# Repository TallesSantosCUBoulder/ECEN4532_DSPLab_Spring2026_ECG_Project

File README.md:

# Module 02 – ECG Project
**ECEN4532: Digital Signal Processing Laboratory (Spring 2026)**  
**Instructor:** Talles Santos  
**Students:**   Alyssa Jackson  
&emsp;&emsp;&emsp;&emsp;&emsp;Joshua Thomas  
&emsp;&emsp;&emsp;&emsp;&emsp;Emilie Teel  

## Introduction
  An electrocardiogram (often shortened to ECG or EKG) procedure is a quick and simple test that is designed to record the eletrical signal from a patient's beating heart and use it to find its natural rhythmic cycle [1]. By placing electrodes aroud the patient's chest, arms, and/or legs, a circuit is created with the heart as the voltage source the contractions caused by electricity are pickeed up by the electrodes and sent to a circuit.

  *Figure 1: A diagram of the different parts of a heartbeat that are searched for during an ECG test [2].*  

  This signal of the heartbeat, in the form of the "PQRST" complex as seen with Figure 1, is what needs to be detected in order to find important information about a patient's heart. Things like poor blood flow, arrhythmias, heart attacks, and thickened heart walls, can be picked up, seen, and diagnosed accurately with this type of circuit [4].  

  The goal of this project is not only to build an analog circuit that can pick up the signals of a heartbeat, but to then transmit that data using an Arduino Uno to MATLAB that will then visual said data from the heart and calculate the BPM (or the beats per minute) from the received signal.

## Methodology

### Hardware

*Figure 2: A diagram of the circuit that a body completes based on the position of the electrodes. A) represents the circuit on a body while B) shows the connections in the image space. [3]*  

As can be seen in Figure 2, the basic premise of the ECG Circuit itself involves building a voltage divider with the heart in order to pick up the signals ans input it into the circuit.

#### Circuit Schematic

To gather the heart rate information from the body leads are attatched to the patient and then connected to an analog circuit to filter and amplify the data coming in from the leads. This circuit is used as a form of preprocessing to alow for a more precise reading from the microcontroller. Below is the schematic of the ECG circuit that was used in its design.

The Schematic of the circuit is broken into parts each playing a role in the amplification, filtering, or offset of the signal for later interpretation. The first segment of the schematic is an instrumentation amplifier to take the very weak signal from the body and give it gain to allow for filtering. The second step is a passive high pass filter made of a capacitor and resistor. This stage is used to reduce interferance from body roll and breathing, and to remove dc offset from the signal. The next stage is a buffer to isolate previos stages from feedback. The following stage is a 60hz notch filter. This filter has a high attenuation of the 60 hz signal to remove interferance from main powr in the room as it is the biggest source of interferance in the signal. This is then fed into a buffer to once again isolate the filter from future stages. The subsiquent stage is an active low pass filter to further attenuate high frequencies such as 60hz and to remove any noise from frequencies not produced by heartrate. The final stage is an inverting amplifier to further amplify the signal for processing, and it is combined with a circuit to add offset so the microcontroller can read the signal.

#### PCB Design

To buid the circuit in hardware the schematic was then used to design the PCB to physically implement the circuit. Below is the PCB schematic that was used in this project.

There was an itterative process used in designing the layout for the PCB. The software used for this was KICAD, and in this software it has the ability to select pieces from the schematic to then place on the PCB. So the circuit was designed piece by piece for each module. The circuit looped arround starting at the bottom left corner with the inputs and moving on to the top left for the output. each of the op amps used were dual op amps and therefor the sequential modules were able to make use of the two amplifiers vutting down on the size of the circuit. The difficult part of the design was making sure that all power inputs and ground planes were connected propperly. Through trial and error the above circuit was compiled.

The hardware was not able to be completed at the time of this paper, but the components have been selected and they will be soldered to the pcb to complete the analog circuit.
### Testing the Hardware

At the time of this paper the circuit was not able to be made due to some issues with the milling machine, but there are further steps for future use when the machine is up and running. The future plans for testing is to print out the PCB, solder on the components, and connect the completed circuit to the simulator and then to one of us to test the output. The output of the circuit will be observed from the ocilloscope and a passed test will be a test that shows a similar result to the already working breadboard circuit. The report will be updated with this information when the tests have been run.
### Software
For the software side of things, an Arduino Uno R3 was used to take that normalized heartbeat signal, or a simple test signal generated from a function generator, that ranges from 0 to 5V and transmit the data to MATLAB via packets. The packets act like individual bundles of data that are all sent to the host computer running MATLAB in order instead of in a constant real time stream that would take more processing power and lead to potential data errors.  

But before the data is sent over, the MATLAB script must be formatted to in order to gather the data coming in from the Arduino at the correct speed and sampling frequency:  

```matlab
% define port; check whatever port the Arduino is connected to
% and uncomment that one while commenting the other ports
portName = serialportlist("available");
% portName = '/dev/ttyACM0' ;
% portName = '/dev/ttyACM1' ;
portName = '/dev/ttyUSB0' ;

% open port
fp = serialport(portName,115200);

% settings
fs = 1 / (3e-3) ;                          % sampling frequency of the arduino
sizeBufferArduino = 20 ;                   % from arduino code
t_Buffer = 10.0 ;                          % in seconds
nSamplesBuffer = round(t_Buffer*fs) ;      % nSamples of the circular buffer in the matlab script
bits2volts = 5/(2^10-1) ;                  % convertion from bits to volts (arduino uno 10 bits)

% initialing variables
CircularBuffer = zeros(nSamplesBuffer,1);
vecSamples = 0 ;
count=1;

``` 
*Code Snipet 1: The first lines from the MATLAB script 'read_serial_Nsamples_buffer.m'. These lines work to format everything from the baud rate being received, the sampling frequency that the signal is being measured at, the size of the data packets that are recieved at once, conversion of the Arduino value from 0 to 5 volts, and other variables needed in the plotting of the data in real-time.* 

That packet of 20 individual values from the Arduino is sent to a loop that can't be left without a Serial port disconnection or a manual code end caused by the user. That loop constantly looks for the start of the new incoming packet, packet into a vector that MATLAB can tranversed, enters that vector being evaluated, turns the value into a voltage thanks to the data conversion with a time attached to the value, and finally plotted on a constantly updating graph of voltage vs. time. A circular buffer is used so that a constant stream of voltages can be plotted in an ever-rotating plot that can be seen in Figure 3 below.

*Figure 3: A gif that shows how the plotting of data works on MATLAB. The red vertical line acts as the real-time sweep as the signal gets plotted.*  

As can also be seen from Figure 3, there are also magneta dots and red and green stars on the signal as well. These are the marks that are meant to point to the what the R peak of a signal is as well as the right(green) and left(red) of that R peak, as explained below:

```matlab
% For the best and most accurate data, the inputted signal need to be 
% filtered first
function [R_loc, left, right, bpm]=identifyQRSComplex(signal,Fs)

R_loc = [];
left = [];
right = [];
bpm = NaN;
%% Preprocessing the signal for QRS detection
x = signal;

% Removing the DC Offset from the Signal
x = x - mean(x);

% Finding the Time Scale of the Signal
T = 1/Fs;
N = length(x);

t = (0:N-1)*T;

% Normalizing the Signal
Norm_signal = x.^2;
Norm_signal = Norm_signal / max(abs(Norm_signal));

% Finding the QRS Complex Peaks
h = ones (1,36)/36; % 0.1secs
% Apply filter
x = conv (Norm_signal ,h,'same');
x = x/max(abs(x));

max_h = max(x);
thresh = 2*mean(x);
poss_reg =(x>thresh*max_h)';

% left = find(diff([0 poss_reg'])==1);
% right = find(diff([poss_reg' 0])==-1);

if isempty(poss_reg)
      left = [];
      right = [];
    else
      left = find(diff([0, poss_reg(:)']) == 1);
      right = find(diff([poss_reg(:)' 0]) == -1);
end

% The R_loc variable is the location of the R values that make up a QRS
% Complex
for i=1:length(left)
    [R_value(i) R_loc(i)] = max(x(left(i):right(i)));
    R_loc(i) = R_loc(i)-1+left(i); % add offset
end

freq_heartbeat = length(left)/max(t);

% Convert frequency to beats per minute
bpm = freq_heartbeat * 60;

end
```
*Code Snipet 2: The 'identifyQRSComplex' function used in the MATLAB code to find the bpm, the R location from the QRS complex, and the left and right of the the R location.*  

The code from the above snipet is the entireity of the function, and it also has the added benefit of being able to calculate the bpm (or the frequency of a signal in the span of a minute) of the input signal, which is displayed at the top of the gif in Figure 3. When combined, the function from Code Snipet 2 and the MATLAB script, the entirity of the code can detect the peaks of a signal, mark its highest point, the immediate left and right of that peak, and the BPM (or the frequency per minute for non-heartbeat signals) of the signal that is detected through the Arduino Uno.

### Testing the Software

Testing the programming for both the Arduino and MATLAB itself is pretty simple: connect the Arduino to PC running the MATLAB script and view the real-time output from the A0 pin.  

*Figure 4: A gif that shows how the plotting of signals to MATLAB. The gif shows the signals from the A0 pin connected to the GND pin, the 5V pin, and just open to the air.*  

As shown with Figure 4, the signal from the Arduino in the different inputs to the A0 pin. In this test, the BPM from the signal means nothing since the Arduino updating from the inputs was slow due to the packets method, so a different test would be needed to see how the BPM calculation would work.  

*Figure 5: The settings used for the test signal input in the Arduino.*  

Instead of just having a DC signal and moving it from 5V to GND very fast by hand, a function generator was used instead and set with the parameter as seen in Figure 5. The gif from Figure 3 is the real-time plotting of the signal generated using the information from Figure 5.

*Figure 6: The image from the MATLAB srcipt running that shows the BPM of the signal, which is around 90 times a second for a minute, or around 1.5Hz.*  

While the BPM can be seen in Figure 3, it is shown again ib Figure 6. The BPM can be seen as 90, or 1.5Hz, which lines up with how the function generator was set up to output. This shows that the BPM calculation, and the software side of the ECG circuit as a whole, is working as intended.

### Connecting the Hardware and Software

## Results

*Figure 7: The image from the MATLAB srcipt running that shows the BPM of the generated heartbeat signal, which is around 60 times per minute, or around 1Hz.*  

Once the circuit board was connected to the Arduino or MATLAB, and the output from Figure 7 with the same BPM as generated from the heartbeat signal generator, it shows that the system works. Despite the little hiccup of the R location marker where the marker is on the lower S spike instead of the R peak, the count of the BPM and the output of the entire system is correct and show that everything works.  

## Conclusion and Future Work

With the overall results of the completed hardware and software integration showing that the accurate heartbeat shape normalized in between 0 and 5V and counting same BPM value that the heartbeat device, it is safe to say that the overall circuit works. Every apsect does what it is supposed to do, despite some flaws.  

The main issues that were had with the ECG circuit as a whole was the slow speed of the "real-time" system and the fact that the MATLAB script counts the bottom part of the QRS complex instead of the R peak like it should. The slow "real-time" data collection issue can be solved with a faster, more powerful computer. The R peak detection, on the other hand, is due to the fact that the heartbeat signal generator isn't completely accurate to an actual heartbeat. An actual heartbeat looks more like the image from Figure 1, with the S peak in the QRS complex being nowhere as large as what the heartbeat generator outputs in normal heartbeats. While most ECG images do look like Figure 1, there are some situations, either with abnormal heartbeats or with the placements of the electrodes [5, 6], a large S peak can occur and have a larger value than the R peak. Due to this oversight in assumption of the QRS complex that has then bleed into the Code Snipet 2 with the 'identityQRSComplex' function, a fix that needs to not only look into the value of the peak but into the positive value while having better checks with the Q and S peaks to better mark on the plot of the signal would be the next step to take. But other than that, this combination of hardware signal detection, filtering, and normalization to software real-time QRS complex detection and BPM calculation works overall.

Due to manufacturing error, the circuit was not completely implemented at the time of this report. Future steps in this reguard are to fix the milling machine by replacing the bits, milling out the PCB, soldering the components, and testing the circuit as related in the testing portion of this report. The hardware and software when both verified to be working will be combined to a full implementation, and the further software implementations will be added. 

## References
[1]&emsp;Mayo Clinic, “Electrocardiogram (ECG or EKG),” Mayoclinic.org, Apr. 02, 2024. https://www.mayoclinic.org/tests-procedures/ekg/about/pac-20384983
‌

[2]&emsp;“How does an ECG work? Understanding ECG and heart health,” Withings.com, 2026. https://www.withings.com/us/en/health-insights/about-ecg-ekg-electrocardiogram?srsltid=AfmBOorydm8yKYhquxItaWKUVDFjAmXBAV8dxPpUkZrdyCu7soVGj3wy (accessed Mar. 22, 2026).
‌

[3]&emsp;Jaakko Malmivuo and R. Plonsey, Bioelectromagnetism : Principles and Applications of Bioelectric and Biomagnetic Fields. New York Oxford University Press -10-05, 1995.
‌

[4]&emsp;“Abnormal Electrocardiogram (ECG/EKG) - Doral Health & Wellness NY,” Doral Health & Wellness, Aug. 08, 2025. https://doralhw.org/condition/abnormal-electrocardiogram-ecg-ekg/ (accessed Mar. 22, 2026).
‌

[5]&emsp;About EMCrit, “Late or irregular R-wave transition,” EMCrit Project, Aug. 07, 2025. https://emcrit.org/ibcc/later/ (accessed Mar. 23, 2026).
‌

[6]&emsp;“The QRS complex: ECG features of the Q-wave, R-wave, S-wave & duration,” ECG & ECHO, May 22, 2018. https://ecgwaves.com/ecg-qrs-complex-q-r-s-wave-duration-interval/
‌

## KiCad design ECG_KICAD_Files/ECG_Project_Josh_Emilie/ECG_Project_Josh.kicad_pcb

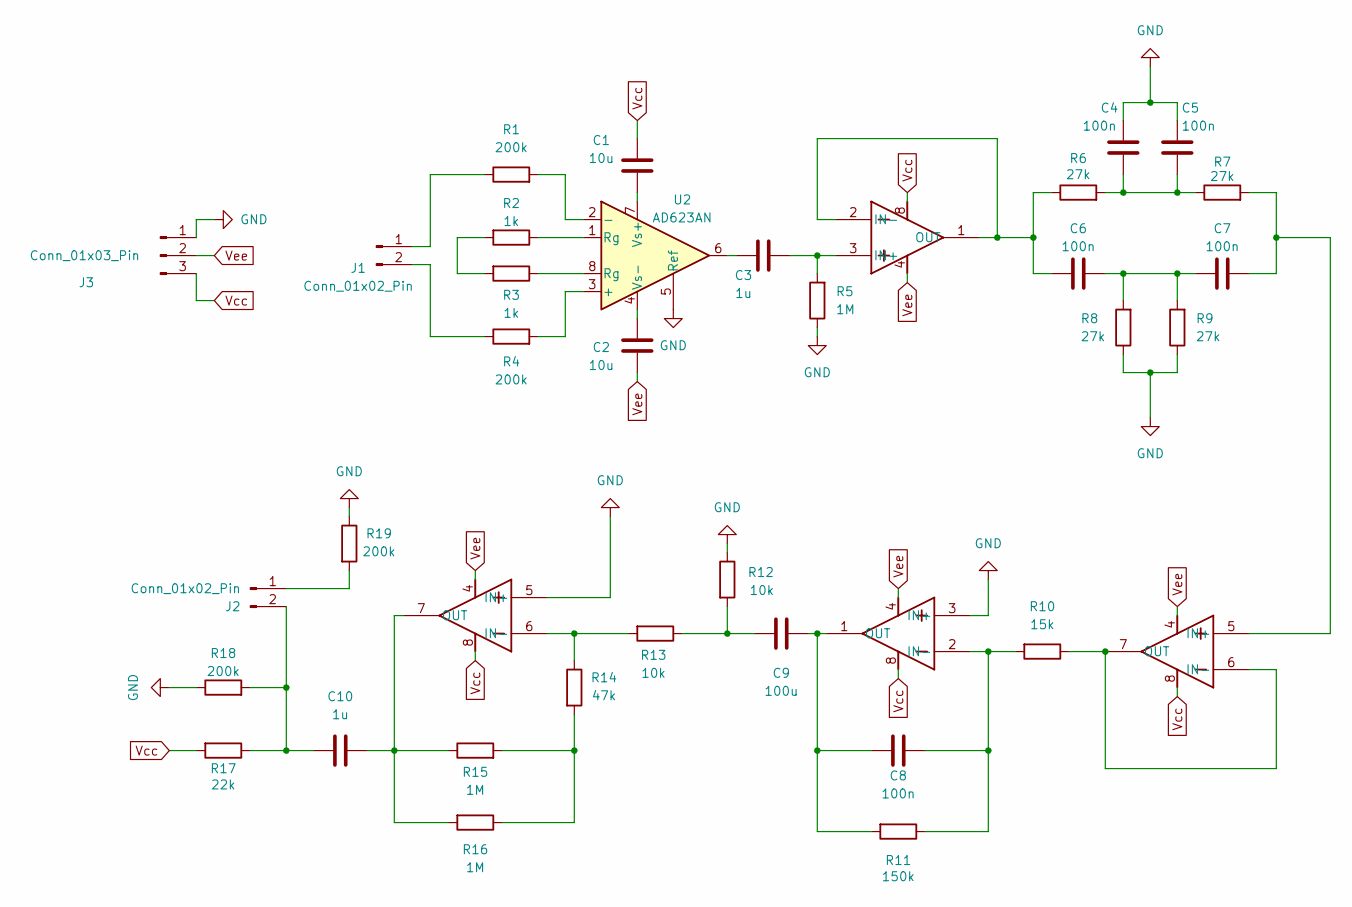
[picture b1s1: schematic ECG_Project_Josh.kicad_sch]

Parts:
C1, C2: 10u; C_Axial_L3.8mm_D2.6mm_P7.50mm_Horizontal
C3, C10: 1u; C_Axial_L3.8mm_D2.6mm_P7.50mm_Horizontal
C4, C5, C6, C7, C8: 100n; C_Axial_L3.8mm_D2.6mm_P7.50mm_Horizontal
C9: 100u; C_Axial_L3.8mm_D2.6mm_P7.50mm_Horizontal
J1, J2: Conn_01x02_Pin; PinHeader_1x02_P2.54mm_Horizontal
J3: Conn_01x03_Pin; PinHeader_1x03_P2.54mm_Horizontal
R1, R4, R18, R19: 200k; R_Axial_DIN0204_L3.6mm_D1.6mm_P7.62mm_Horizontal
R2, R3: 1k; R_Axial_DIN0204_L3.6mm_D1.6mm_P7.62mm_Horizontal
R5, R15, R16: 1M; R_Axial_DIN0204_L3.6mm_D1.6mm_P7.62mm_Horizontal
R6, R7, R8, R9: 27k; R_Axial_DIN0204_L3.6mm_D1.6mm_P7.62mm_Horizontal
R10: 15k; R_Axial_DIN0204_L3.6mm_D1.6mm_P7.62mm_Horizontal
R11: 150k; R_Axial_DIN0204_L3.6mm_D1.6mm_P7.62mm_Horizontal
R12, R13: 10k; R_Axial_DIN0204_L3.6mm_D1.6mm_P7.62mm_Horizontal
R14: 47k; R_Axial_DIN0204_L3.6mm_D1.6mm_P7.62mm_Horizontal
R17: 22k; R_Axial_DIN0204_L3.6mm_D1.6mm_P7.62mm_Horizontal
U1, U3: LF412ACN/NOPB; DIP-8_W7.62mm
U2: AD623AN; DIP-8_W7.62mm

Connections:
GND: C4.2, C5.2, J3.1, R5.1, R8.1, R9.1, R12.1, R18.1, R19.1, U2.5 (Ref), U3.3 (IN+), U3.5 (IN+)
unnamed: C3.1, U2.6
unnamed: C4.1, C5.1, R6.2, R7.1
unnamed: C6.1, C7.2, R8.2, R9.2
unnamed: C9.2, R12.2, R13.1
unnamed: J1.1, R1.1
unnamed: J1.2, R4.1
unnamed: J2.1, R19.2
unnamed: C10.1, J2.2, R17.1, R18.2
unnamed: R2.1, U2.1 (Rg)
unnamed: R2.2, R3.2
unnamed: R3.1, U2.8 (Rg)
unnamed: R14.2, R15.2, R16.1
unnamed: C3.2, R5.2, U1.3 (IN+)
unnamed: C6.2, R6.1, U1.1 (OUT), U1.2 (IN-)
unnamed: C7.1, R7.2, U1.5 (IN+)
unnamed: R10.1, U1.6 (IN-), U1.7 (OUT)
unnamed: R4.2, U2.3 (+)
unnamed: R1.2, U2.2 (-)
unnamed: C1.2, U2.7 (Vs+)
unnamed: C2.2, U2.4 (Vs-)
unnamed: C8.1, R10.2, R11.1, U3.2 (IN-)
unnamed: C8.2, C9.1, R11.2, U3.1 (OUT)
unnamed: R13.2, R14.1, U3.6 (IN-)
unnamed: C10.2, R15.1, R16.2, U3.7 (OUT)
Vcc: C1.1, J3.3, R17.2, U1.8, U3.8
Vee: C2.1, J3.2, U1.4, U3.4

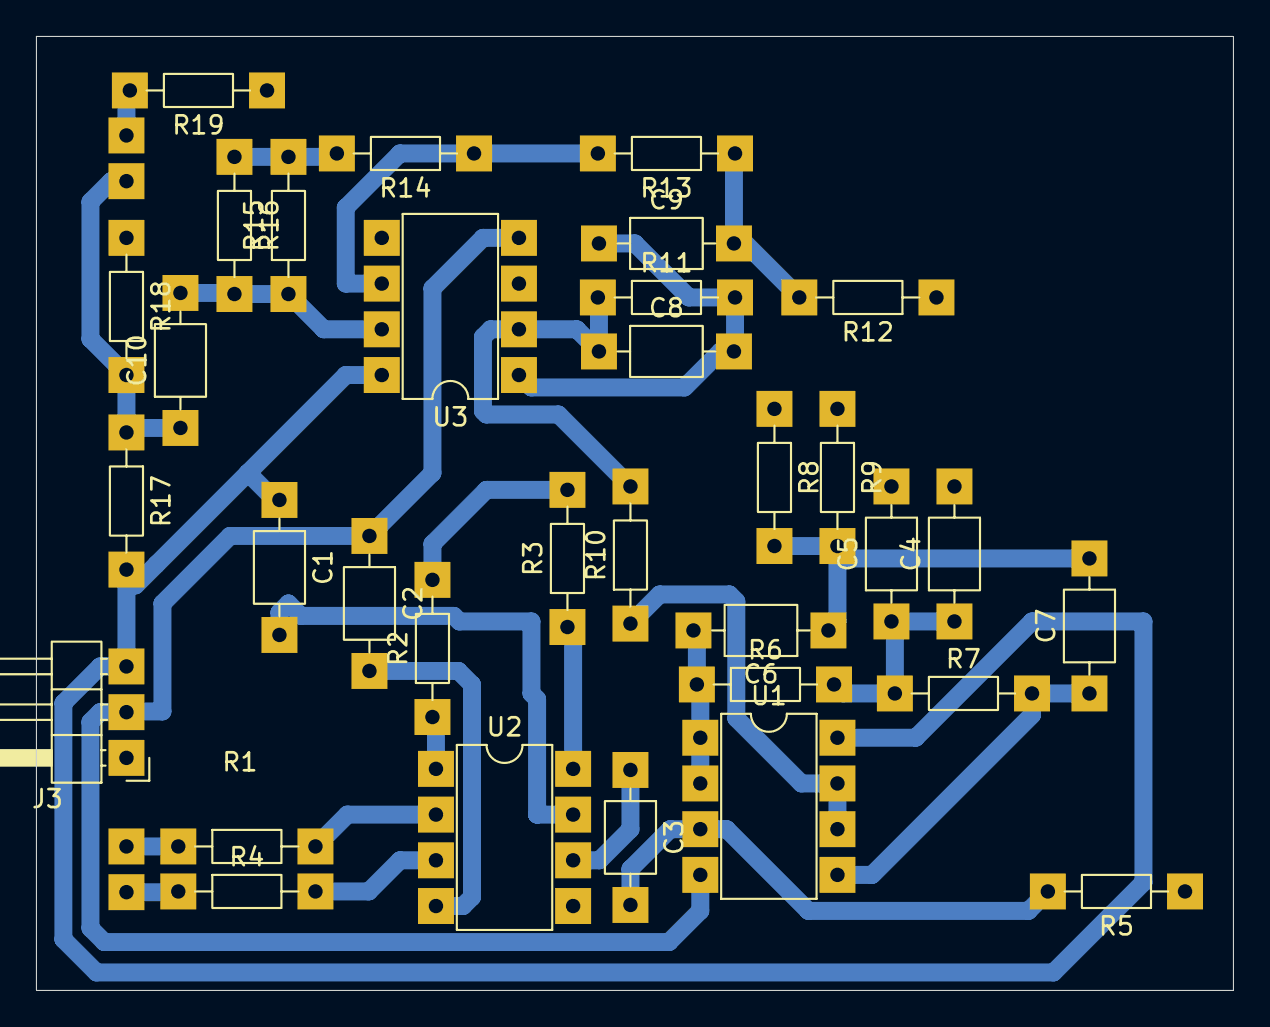
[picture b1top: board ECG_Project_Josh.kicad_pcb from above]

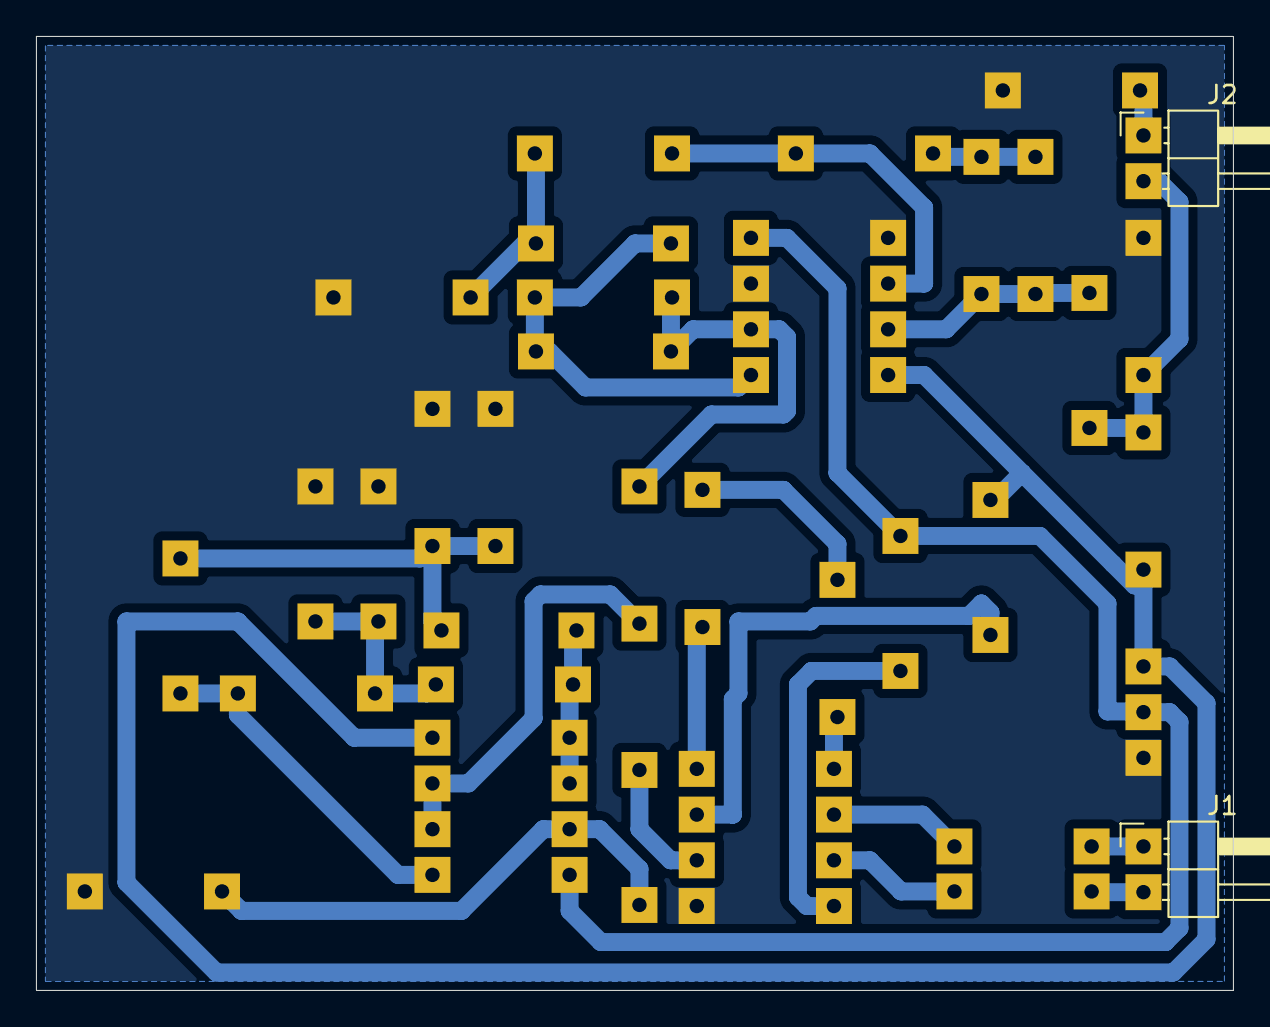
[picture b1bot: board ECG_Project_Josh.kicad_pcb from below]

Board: 2 copper layers, 66.5 x 53.0 mm, 35 parts (2 on the bottom side), 27 nets.

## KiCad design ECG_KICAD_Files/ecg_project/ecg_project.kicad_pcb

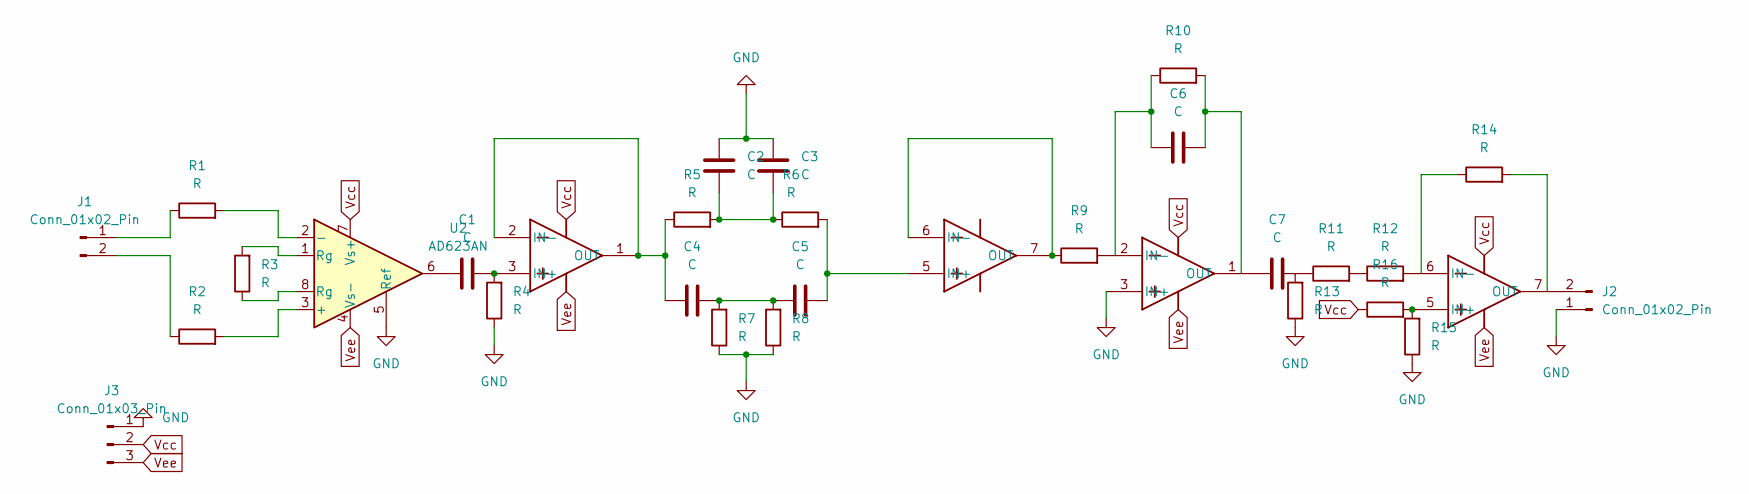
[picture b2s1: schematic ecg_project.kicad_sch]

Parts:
C1, C2, C3, C4, C5, C6, C7: C; C_Axial_L3.8mm_D2.6mm_P7.50mm_Horizontal
J1, J2: Conn_01x02_Pin; PinHeader_1x02_P2.54mm_Horizontal
J3: Conn_01x03_Pin; PinHeader_1x03_P2.54mm_Horizontal
R1, R2, R3, R4, R5, R6, R7, R8, R9, R10, R11, R12, R13, R14, R15, R16: R; R_Axial_DIN0204_L3.6mm_D1.6mm_P7.62mm_Horizontal
U1, U3: LF412ACN/NOPB; N08E
U2: AD623AN; DIP-8_W7.62mm

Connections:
GND: C2.2, C3.2, J2.1, J3.1, R4.1, R7.1, R8.1, R13.1, R15.1, U2.5 (Ref), U3.3 (IN+)
unnamed: C1.1, U2.6
unnamed: C2.1, C3.1, R5.2, R6.1
unnamed: C4.1, C5.2, R7.2, R8.2
unnamed: C6.1, R10.1
unnamed: C6.2, R10.2
unnamed: C7.2, R11.1
unnamed: J1.1, R1.1
unnamed: J1.2, R2.1
unnamed: J2.2, U3.7 (OUT)
unnamed: R3.1, U2.8 (Rg)
unnamed: R3.2, U2.1 (Rg)
unnamed: R11.2, R12.1
unnamed: C1.2, R4.2, U1.3 (IN+)
unnamed: C4.2, R5.1, U1.1 (OUT), U1.2 (IN-)
unnamed: C5.1, R6.2, U1.5 (IN+)
unnamed: R9.1, U1.6 (IN-), U1.7 (OUT)
unnamed: R2.2, U2.3 (+)
unnamed: R1.2, U2.2 (-)
unnamed: R9.2, U3.2 (IN-)
unnamed: C7.1, U3.1 (OUT)
unnamed: R15.2, R16.2, U3.5 (IN+)
unnamed: R12.2, U3.6 (IN-)
Vcc: J3.2, R16.1, U2.7 (Vs+)
Vee: J3.3, U2.4 (Vs-)

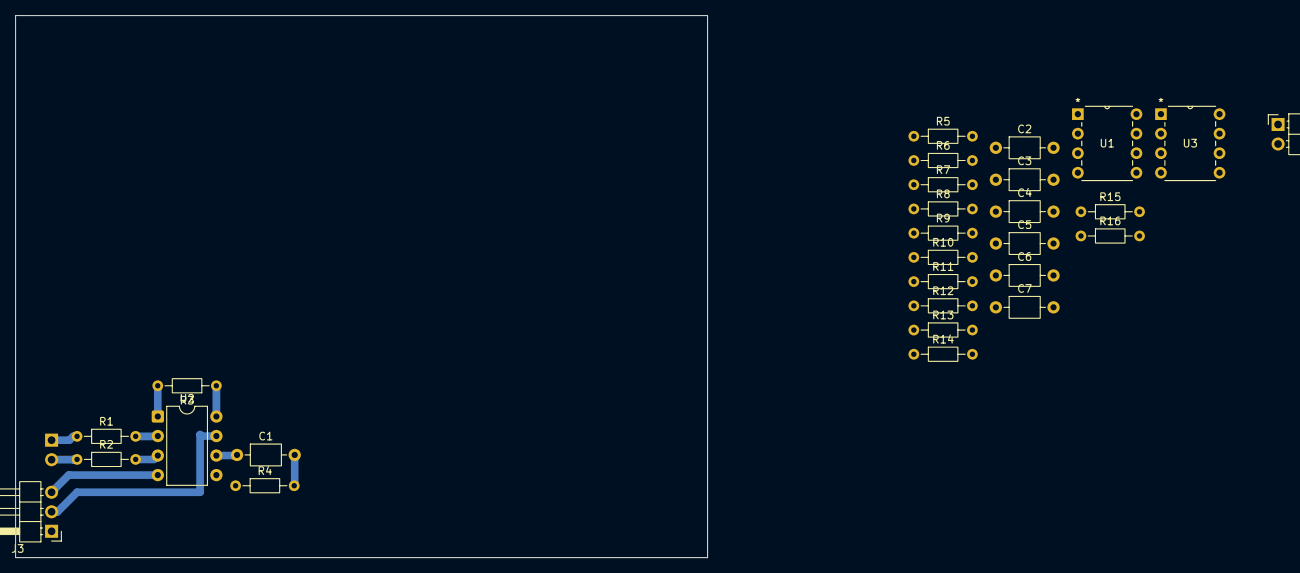
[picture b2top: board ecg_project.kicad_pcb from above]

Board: 2 copper layers, 90.0 x 70.5 mm, 29 parts (1 on the bottom side), 25 nets.

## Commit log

2026-02-17 Update Readme file.
2026-02-17 Create a directory to work on the hadware-software interface
2026-02-17 First Version of the hadware-software interface.
2026-02-17 ECG Schematic folder update
2026-02-19 read serial port routines were updated..
2026-02-20 Trying to troubleshoot the code
2026-02-24 Example ECG Code
2026-02-24 ECG file example..
2026-02-24 Created Matlab Function the Fincd the QRS Complex
2026-02-25 Updating the Matlab Serial code with the new function
2026-02-26 Op and Instrumentation amps documentation
2026-02-26 Small Fixes in the MatLab Code
2026-03-01 schematic update
2026-03-05 Work done to the Code and Readme report
2026-03-05 Report Basic outline
2026-03-05 Report Beginning
2026-03-05 Formatting Change
2026-03-05 Format
2026-03-05 Brief Introduction Beginning
2026-03-05 Format Change
2026-03-05 Inseting an image
2026-03-05 Folder for Images Created
2026-03-05 Fixing image attempt
2026-03-05 Added alt text
2026-03-05 Fixed image (hopefully)
2026-03-05 Redo images folder
2026-03-05 image fix attempt 2: the electric bogaloo
2026-03-05 Image fix: third times the charm
2026-03-05 image captions added
2026-03-05 More explanations and images
2026-03-12 Images for Report and Finalized Matlab code
2026-03-12 Report Formatting Changes
2026-03-12 Adding code to the report
2026-03-12 Some Code Renaming, rearraging, and report update
2026-03-12 Report Update
2026-03-12 Major Progress on the report
2026-03-12 smaller update
2026-03-13 Adding more images and updating the readme
2026-03-16 josh schematic update
2026-03-16 pin update for symbol
2026-03-22 Finished the Introduction
2026-03-22 Update to the code and report
2026-03-22 New gif and update to software testing in report
2026-03-22 Second software test
2026-03-22 Project Requirements updates and Report Testing Software update
2026-03-22 Reference Update and Results Update, and started the presentation folder
2026-03-22 Added References folder and updated references in teh report
2026-03-22 Adding image and testing tab spacing
2026-03-22 Spacing updates for the report
2026-03-22 Spacing update on report
2026-03-22 Image added to the report
2026-03-22 Photo update report
2026-03-23 Flawless MATLAB Script and finished software side of the Report
2026-03-23 Fixed the references for the report
2026-03-23 Small change to the report
2026-03-23 Small Report
2026-03-24 PCB Complete DRM Passed
2026-03-24 Gerber and Drll files generated
2026-03-24 rename
